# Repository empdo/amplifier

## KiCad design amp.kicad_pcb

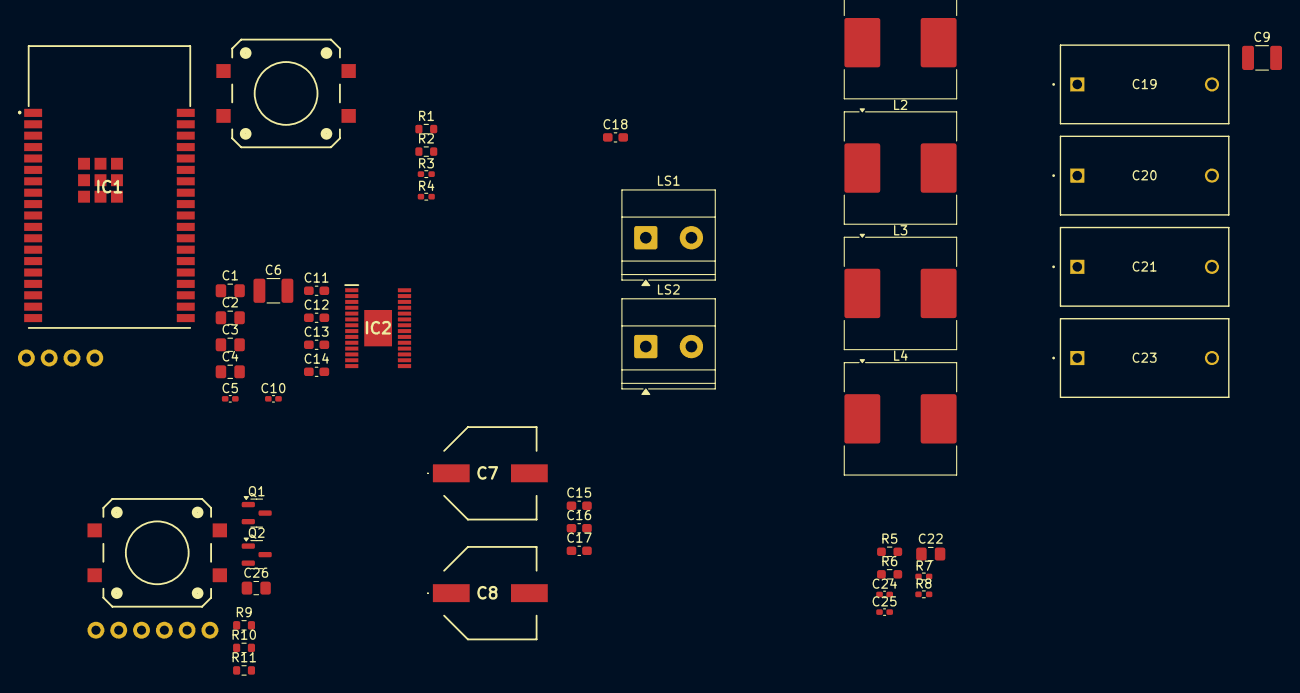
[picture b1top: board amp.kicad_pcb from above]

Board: 2 copper layers, 51 parts (0 on the bottom side), 36 nets, no tracks yet.

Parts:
C1, C2, C4, C26: 0.1uF; C_0805_2012Metric_Pad1.18x1.45mm_HandSolder
C3: TBD; C_0805_2012Metric_Pad1.18x1.45mm_HandSolder
C5, C10, C24, C25: 0.1uF; C_0402_1005Metric_Pad0.74x0.62mm_HandSolder
C6, C9: 22uF; C_1210_3225Metric_Pad1.33x2.70mm_HandSolder
C7, C8: EEE-FPV391UAP; EEE0JA152UAP
C11: 4.7uF; C_0603_1608Metric_Pad1.08x0.95mm_HandSolder
C12: 0.1uF; C_0603_1608Metric_Pad1.08x0.95mm_HandSolder
C13, C14: 1uF; C_0603_1608Metric_Pad1.08x0.95mm_HandSolder
C15, C16, C17, C18: 0.22uF; C_0603_1608Metric_Pad1.08x0.95mm_HandSolder
C19, C20, C21, C23: R75G; CAP_R75_18.5X8.5_15_KEM
C22: 22uF; C_0805_2012Metric_Pad1.18x1.45mm_HandSolder
IC1: ESP32-WROVER-E; ESP32WROVERE
IC2: TAS5805MPWP; SOP65P640X120-29N
J1: UART; 1x04_P2.54mm
J2: Conn_01x06; 1x06_P2.54mm
L1, L2, L3, L4: 10uH; L_Coilcraft_MSS1278-XXX
LS1, LS2: Speaker; TerminalBlock_Phoenix_MKDS-1,5-2-5.08_1x02_P5.08mm_Horizont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
Q1, Q2: BC847; SOT-23
R1: 10kR; R_0603_1608Metric
R2, R9: 0R; R_0603_1608Metric
R3: 10k; R_0402_1005Metric_Pad0.72x0.64mm_HandSolder
R4: 4.7k; R_0402_1005Metric_Pad0.72x0.64mm_HandSolder
R5, R6: 4.7k; R_0603_1608Metric_Pad0.98x0.95mm_HandSolder
R7, R8: 10R; R_0402_1005Metric_Pad0.72x0.64mm_HandSolder
R10, R11: 12K; R_0603_1608Metric
SW1, SW3: SMD_12x12mm_h8.5mm; Push_SMD_12x12mm

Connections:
/ADR/FAULT: IC1.6 (IO34), IC2.3 (ADR/~FAULT), R4.2
/DTR: J2.5, Q2.2 (E), R10.1
/EN: C3.1, IC1.3 (EN), Q1.3 (C), R1.2, R2.2
/IO0: Q2.3 (C), R9.2
/LRCLK: IC1.10 (IO25), IC2.6 (LRCLK)
/PVDD: C5.2, C6.2, C7.1 (+), C8.1 (+), C9.1, C10.2, IC2.15 (PVDD_1), IC2.16 (PVDD_2), IC2.27 (PVDD_3), IC2.28 (PVDD_4)
/RTS: J2.6, Q1.2 (E), R11.1
/RXD0: IC1.34 (RXD0), J2.4
/SCL: IC1.37 (IO23), IC2.11 (SCL), R6.2
/SCLK: IC1.11 (IO26), IC2.7 (SCLK)
/SDA: IC1.33 (IO21), IC2.10 (SDA), R5.2
/SDIN: IC1.36 (IO22), IC2.8 (SDIN)
/TXD0: IC1.35 (TXD0), J2.3
//PDN: IC1.12 (IO27), IC2.12 (~PDN), R3.2
DVDD: C1.1, C2.1, C11.2, C12.2, C22.2, IC1.2 (3V3), IC2.2 (DVDD), R1.1, R3.1, R4.1, R5.1, R6.1
GND: C1.2, C2.2, C3.2, C4.1, C5.1, C6.1, C7.2 (-), C8.2 (-), C9.2, C10.1, C11.1, C12.1, C13.1, C14.1, C19.1, C20.2, C21.2, C22.1, C23.1, C26.1, IC1.1 (GND_1), IC1.15 (GND_2), IC1.38 (GND_3), IC1.39 (GND_4), IC1.40 (GND_5), IC1.41 (GND_6), IC1.42 (GND_7), IC1.43 (GND_8), IC1.44 (GND_9), IC1.45 (GND_10), IC1.46 (GND_11), IC1.47 (GND_12), IC2.1 (DGND_1), IC2.5 (DGND_2), IC2.14 (AGND), IC2.19 (PGND_1), IC2.24 (PGND_2), IC2.29 (THERMAL_PAD), J2.1, SW1.1, SW3.1
unnamed: C4.2, R2.1, SW1.2
unnamed: C19.2, C24.1, L4.2, LS2.2
unnamed: C20.1, L1.2, LS1.1, R7.1
unnamed: C21.1, C25.1, L2.2, LS1.2
unnamed: C23.2, L3.2, LS2.1, R8.1
unnamed: C24.2, R8.2
unnamed: C25.2, R7.2
unnamed: C26.2, R9.1, SW3.2
unnamed: C13.2, IC2.13 (AVDD)
unnamed: C17.2, IC2.25 (BST_A+)
unnamed: C16.2, IC2.22 (BST_A-)
unnamed: C18.2, IC2.18 (BST_B+)
unnamed: C15.2, IC2.21 (BST_B-)
unnamed: C17.1, IC2.26 (OUT_A+), L1.1
unnamed: C16.1, IC2.23 (OUT_A-), L2.1
unnamed: C18.1, IC2.17 (OUT_B+), L4.1
unnamed: C15.1, IC2.20 (OUT_B-), L3.1
unnamed: C14.2, IC2.4 (VR_DIG)
unnamed: Q1.1 (B), R10.2
unnamed: Q2.1 (B), R11.2
